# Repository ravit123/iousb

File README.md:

IOUSB
==============
USB extending module based on ATmega8
including:
- 4 digital IO
- 4 analog inputs
- 2 analog outputs
- 2 PWM outputs
- SPI
- I2C
- USART

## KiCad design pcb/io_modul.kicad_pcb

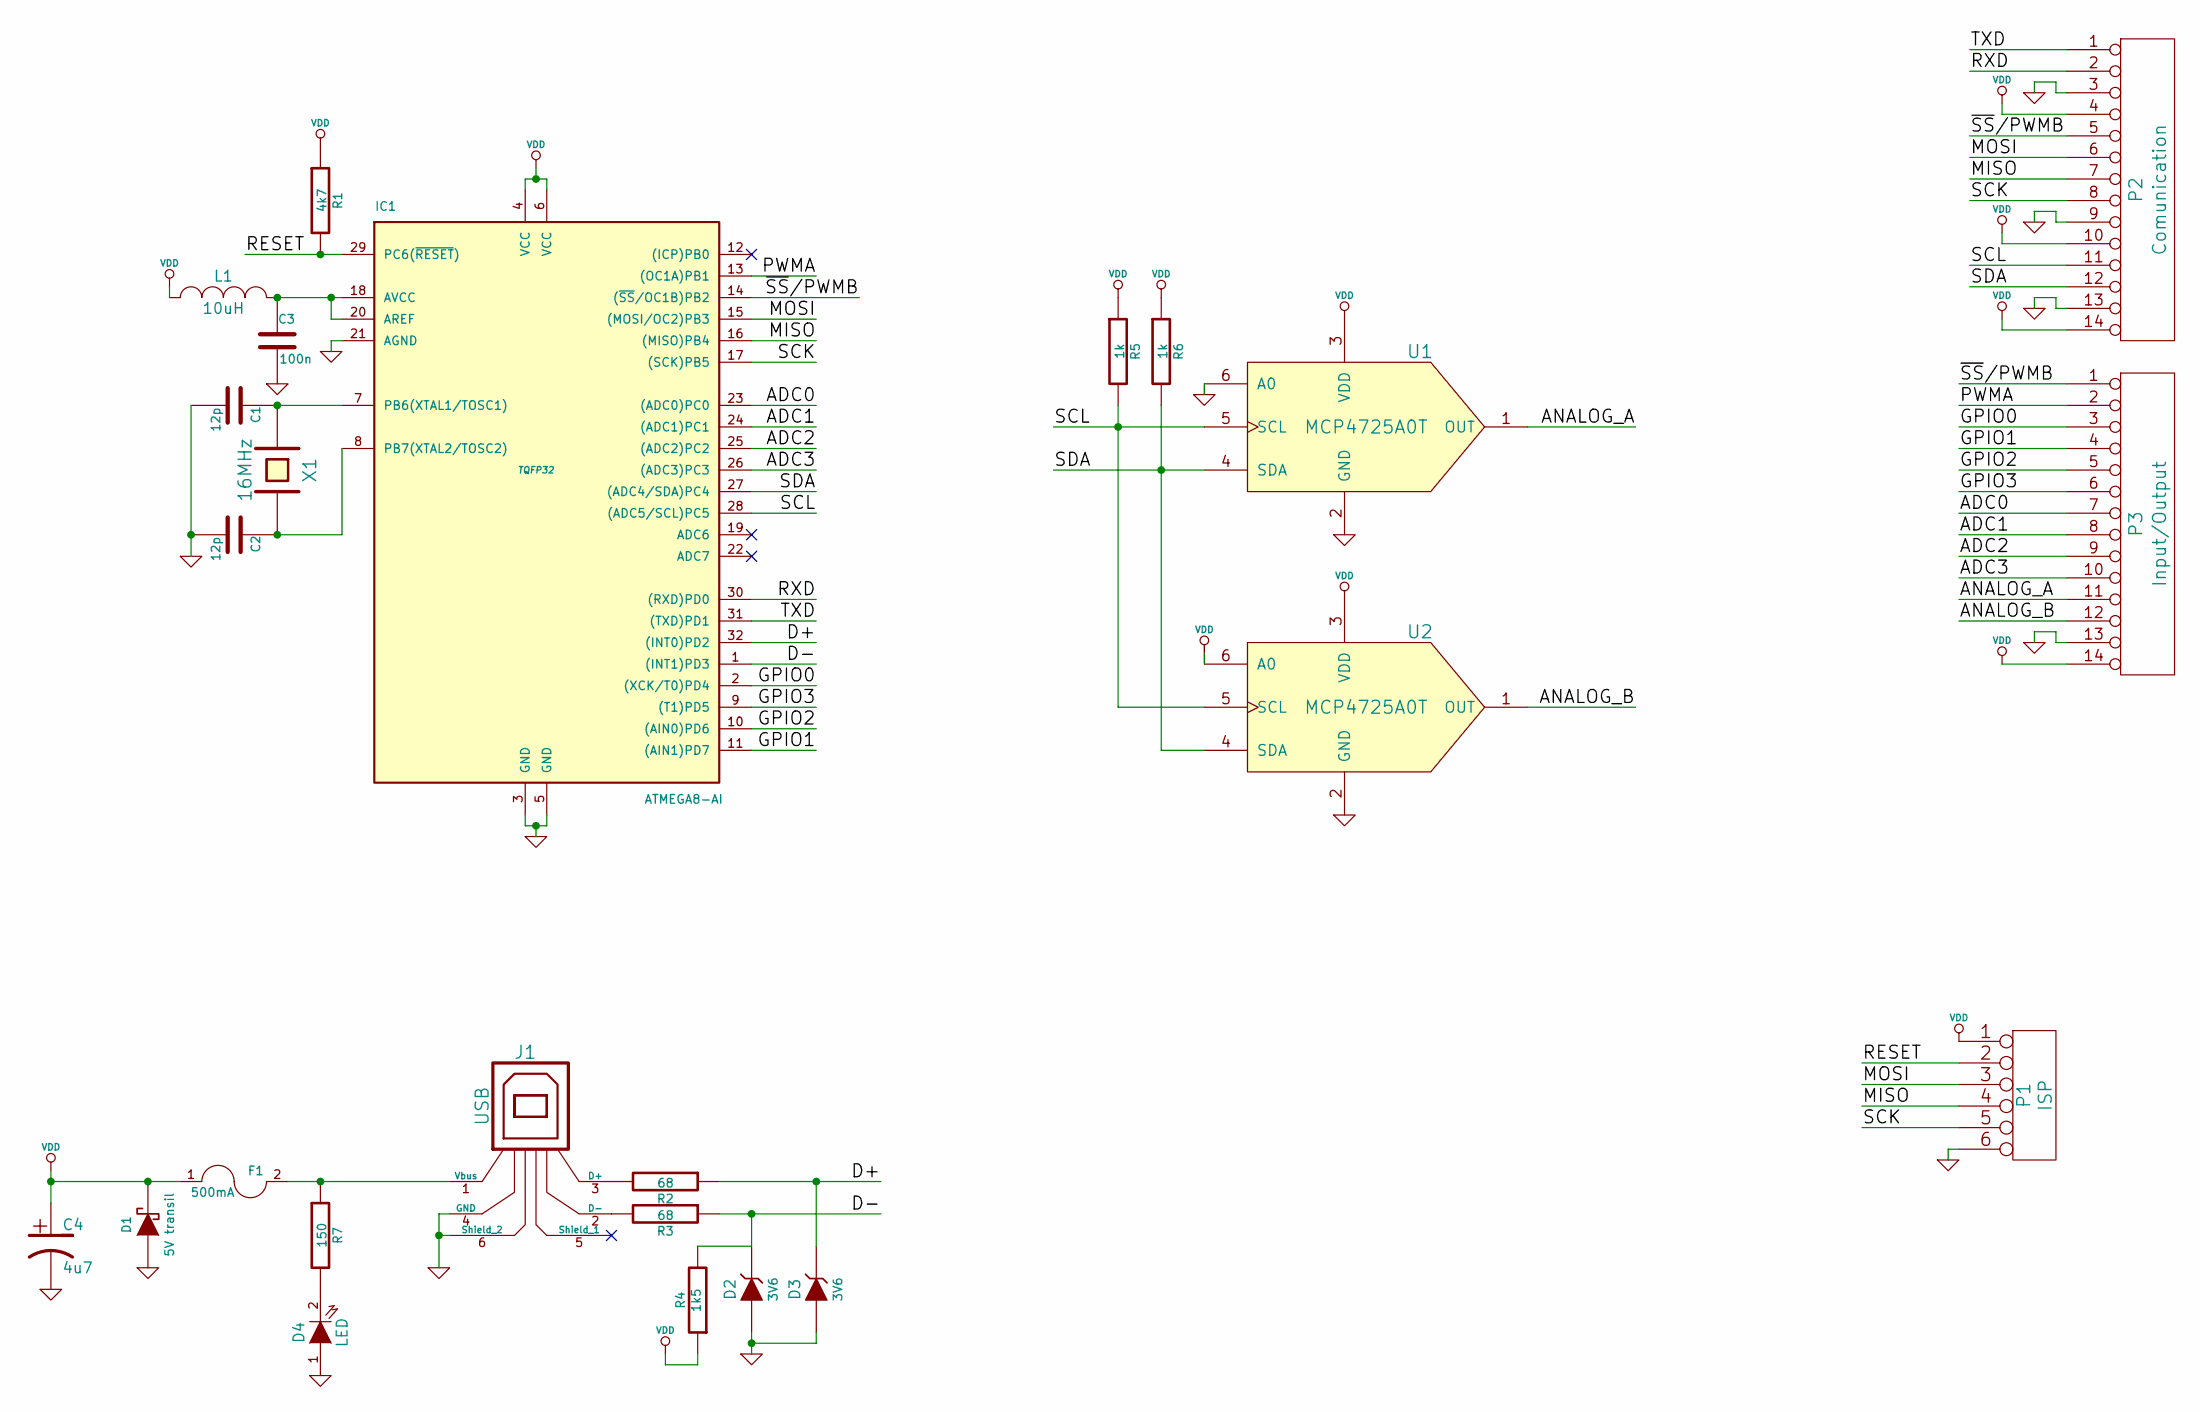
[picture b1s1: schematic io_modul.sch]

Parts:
C1, C2: 12p
C3: 100n
C4: 4u7
D1: 5V transil
D2, D3: 3V6
D4: LED
F1: 500mA
IC1: ATMEGA8-AI; TQFP32
J1: USB
L1: 10uH
P1: ISP
P2: Comunication
P3: Input/Output
R1: 4k7
R2, R3: 68
R4: 1k5
R5, R6: 1k
R7: 150
U1, U2: MCP4725A0T
X1: 16MHz

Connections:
/ADC0: IC1.23 ((ADC0)PC0), P3.7
/ADC1: IC1.24 ((ADC1)PC1), P3.8
/ADC2: IC1.25 ((ADC2)PC2), P3.9
/ADC3: IC1.26 ((ADC3)PC3), P3.10
/ANALOG_A: P3.11, U1.1 (OUT)
/ANALOG_B: P3.12, U2.1 (OUT)
/D+: D3.2 (K), IC1.32 ((INT0)PD2), R2.1
/D-: D2.2 (K), IC1.1 ((INT1)PD3), R3.1, R4.2
/GPIO0: IC1.2 ((XCK/T0)PD4), P3.3
/GPIO1: IC1.11 ((AIN1)PD7), P3.4
/GPIO2: IC1.10 ((AIN0)PD6), P3.5
/GPIO3: IC1.9 ((T1)PD5), P3.6
/MISO: IC1.16 ((MISO)PB4), P1.4, P2.7
/MOSI: IC1.15 ((MOSI/OC2)PB3), P1.3, P2.6
/PWMA: IC1.13 ((OC1A)PB1), P3.2
/RESET: IC1.29 (PC6(~RESET~)), P1.2, R1.2
/RXD: IC1.30 ((RXD)PD0), P2.2
/SCK: IC1.17 ((SCK)PB5), P1.5, P2.8
/SCL: IC1.28 ((ADC5/SCL)PC5), P2.11, R5.2, U1.5 (SCL), U2.5 (SCL)
/SDA: IC1.27 ((ADC4/SDA)PC4), P2.12, R6.2, U1.4 (SDA), U2.4 (SDA)
/TXD: IC1.31 ((TXD)PD1), P2.1
/~SS~/PWMB: IC1.14 ((~SS~/OC1B)PB2), P2.5, P3.1
GND: C1.2, C2.2, C3.2, C4.2, D1.1 (A), D2.1 (A), D3.1 (A), D4.1 (A), IC1.3 (GND), IC1.5 (GND), IC1.21 (AGND), J1.4 (GND), J1.6 (Shield_2), P1.6, P2.3, P2.9, P2.13, P3.13, U1.2 (GND), U1.6 (A0), U2.2 (GND)
unnamed: C1.1, IC1.7 (PB6(XTAL1/TOSC1)), X1.1
unnamed: C2.1, IC1.8 (PB7(XTAL2/TOSC2)), X1.2
unnamed: C3.1, IC1.18 (AVCC), IC1.20 (AREF), L1.2
unnamed: D4.2 (K), R7.2
unnamed: F1.2, J1.1 (Vbus), R7.1
unnamed: J1.2 (D-), R3.2
unnamed: J1.3 (D+), R2.2
VDD: C4.1, D1.2 (K), F1.1, IC1.4 (VCC), IC1.6 (VCC), L1.1, P1.1, P2.4, P2.10, P2.14, P3.14, R1.1, R4.1, R5.1, R6.1, U1.3 (VDD), U2.3 (VDD), U2.6 (A0)

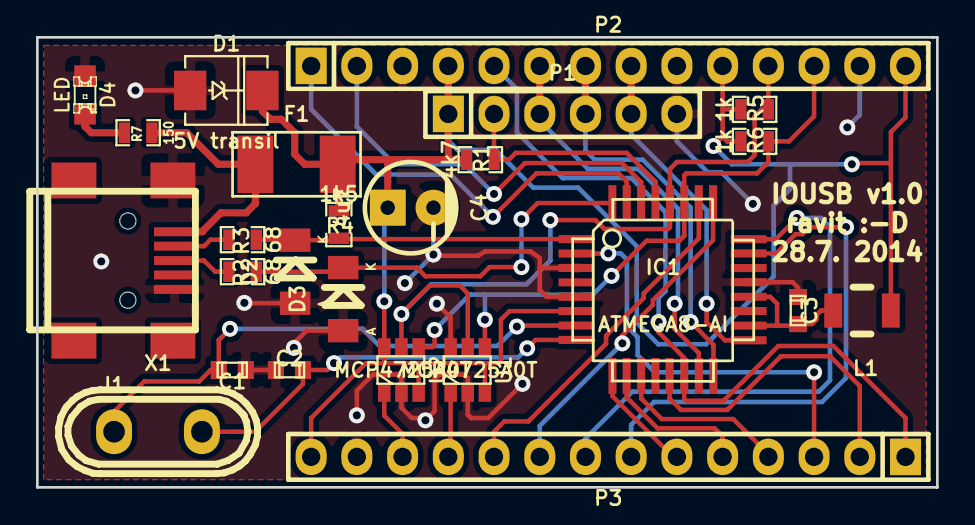
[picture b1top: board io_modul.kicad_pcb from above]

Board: 2 copper layers, 50.0 x 25.0 mm, 25 parts (0 on the bottom side), 31 nets.

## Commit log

2014-07-27 zaklad
2014-07-27 uprava README
2014-07-28 added licence file to root dir
2014-07-31 added usb to GUI
2014-07-31 PCB modified
